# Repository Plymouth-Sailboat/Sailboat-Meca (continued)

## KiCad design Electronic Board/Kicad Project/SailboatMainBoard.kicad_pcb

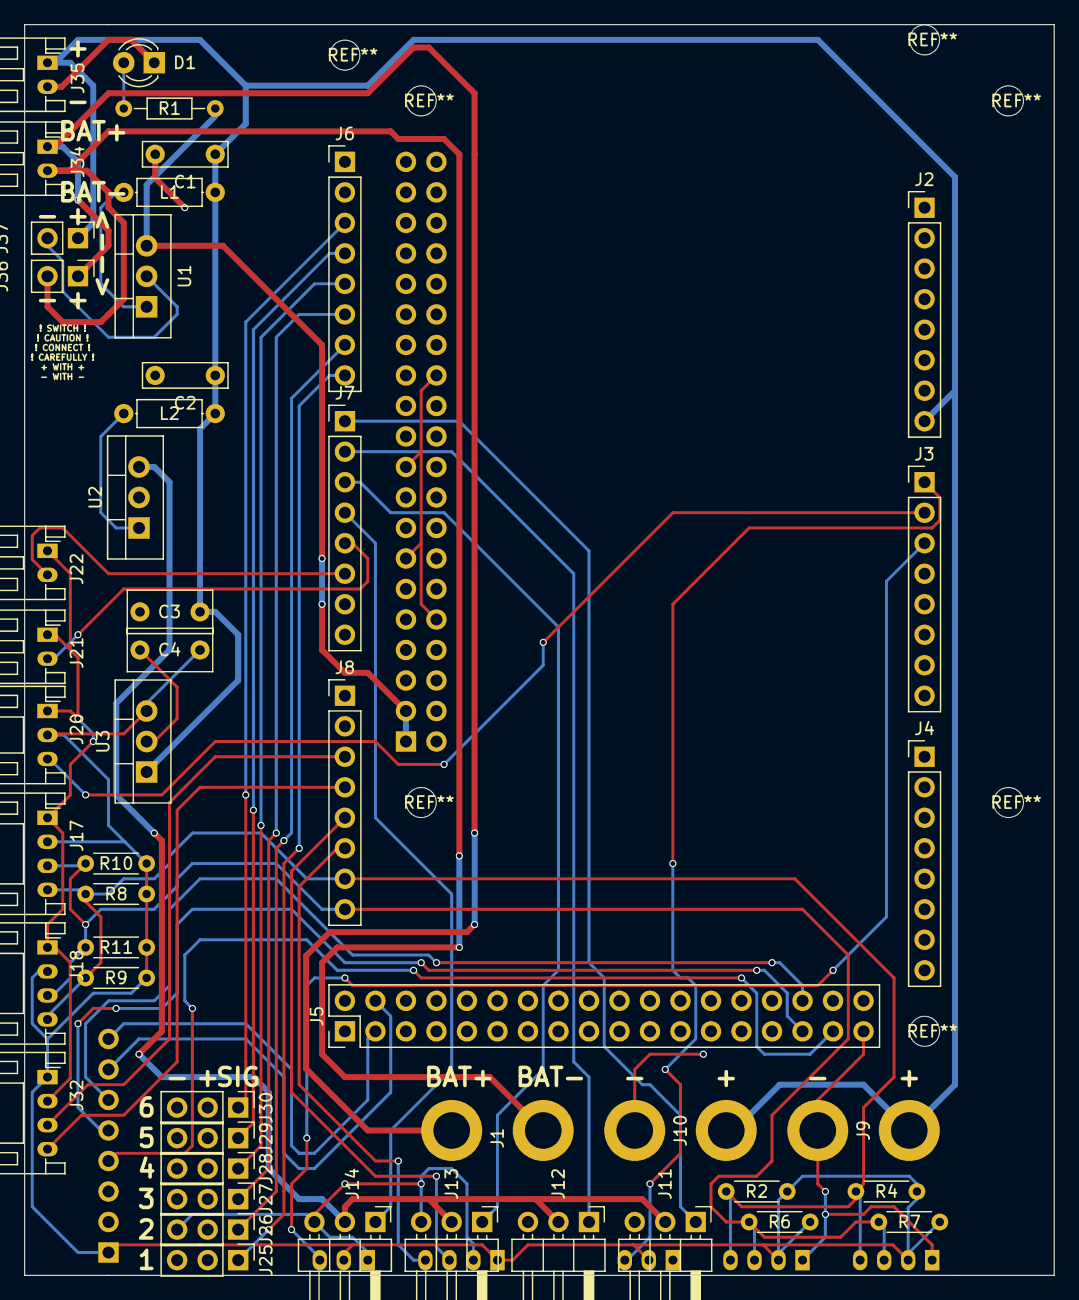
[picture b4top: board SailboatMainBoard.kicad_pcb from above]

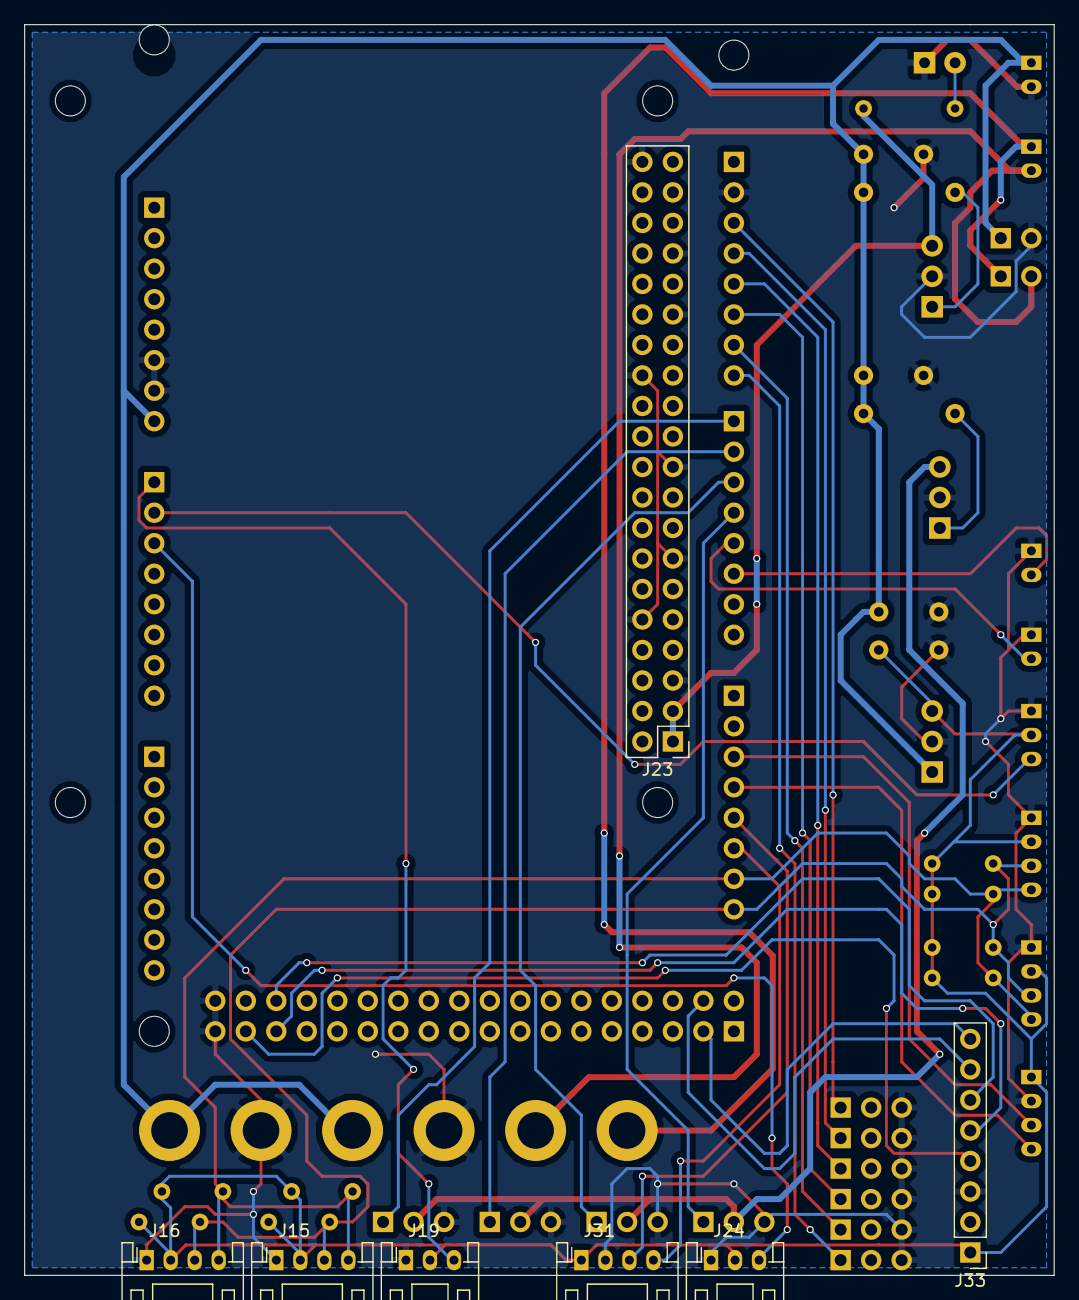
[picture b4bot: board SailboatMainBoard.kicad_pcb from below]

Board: 2 copper layers, 85.7 x 104.1 mm, 56 parts (7 on the bottom side), 36 nets.

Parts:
C1, C2: 4.7uF; C_Rect_L7.0mm_W2.0mm_P5.00mm
C3: 0.33uF; C_Rect_L7.0mm_W3.5mm_P5.00mm
C4: 0.1uF; C_Rect_L7.0mm_W3.5mm_P5.00mm
D1: G; LED_D3.0mm
J1, J9, J10: Conn_01x02; BAT-CONN
J2, J3, J4, J6, J7, J8: Conn_01x08; Pin_Header_Straight_1x08_Pitch2.54mm
J5: Conn_02x18_Odd_Even; Pin_Header_Straight_2x18_Pitch2.54mm
J11, J12, J13, J14: Conn_01x03_Male; Pin_Header_Angled_1x03_Pitch2.54mm
J15, J16, J17, J18, J31, J32: Conn_01x04; JST_PH_S4B-PH-K_04x2.00mm_Angled
J19, J20, J24: Conn_01x03; JST_PH_S3B-PH-K_03x2.00mm_Angled
J21, J22, J34, J35: Conn_01x02; JST_PH_S2B-PH-K_02x2.00mm_Angled
J23: Conn_02x20_Odd_Even; Pin_Header_Straight_2x20_Pitch2.54mm
J25, J26, J27, J28, J29, J30: Conn_01x03_Female; Socket_Strip_Straight_1x03_Pitch2.54mm
J33: Conn_01x08_Female; Socket_Strip_Straight_1x08_Pitch2.54mm
J36, J37: Conn_01x02; Pin_Header_Straight_1x02_Pitch2.54mm
L1, L2: 3.3uH; L_Axial_L5.3mm_D2.2mm_P7.62mm_Horizontal_Vishay_IM-1
R1: 330; R_Axial_DIN0204_L3.6mm_D1.6mm_P7.62mm_Horizontal
R2, R4, R6, R7, R8, R9, R10, R11: 4k7; R_Axial_DIN0204_L3.6mm_D1.6mm_P5.08mm_Horizontal
U1, U2, U3: L7805; TO-220-3_Vertical

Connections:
5V_RPi: J23.1, J23.3, R1.2, U1.3
/Connectors/5V-Sensors: C4.1, J15.2, J16.2, J17.2, J18.2, J19.2, J20.2, J24.2, J31.1, J32.1, J33.1, R2.1, R4.1, R6.1, R7.1, R8.1, R9.1, R10.1, R11.1, U3.3
/Connectors/5V-Servo: J11.2, J12.2, J13.2, J14.2, U2.3
A0: J3.1, J19.3
A1: J3.2, J20.3
A2: J3.3, J24.3
BAT+: C1.1, C2.1, C3.1, J2.8, J9.2, J10.2, J35.1, J37.1, L1.2, L2.2, U3.1
CD: J5.3, J33.8
CS: J5.4, J33.7
D0: J7.5, J21.2
D1: J7.6, J22.2
GND: C1.2, C2.2, C3.2, C4.2, D1.1, J2.6, J2.7, J5.35, J5.36, J6.2, J9.1, J10.1, J11.3, J12.3, J13.3, J14.3, J15.1, J16.1, J17.1, J18.1, J19.1, J20.1, J21.1, J22.1, J23.5, J23.10, J23.13, J23.19, J23.26, J23.29, J23.33, J23.40, J24.1, J25.3, J26.3, J27.3, J28.3, J29.3, J30.3, J31.2, J32.2, J33.3, J35.2, J37.2, U1.2, U2.2, U3.2
MISO: J5.31, J33.5
MOSI: J5.32, J33.6
unnamed: D1.2, R1.1
unnamed: J1.1, J34.1, J36.1
unnamed: J1.2, J34.2, J36.2
unnamed: L1.1, U1.1
unnamed: L2.1, U2.1
RC1: J6.8, J25.1
RC2: J6.7, J26.1
RC3: J6.6, J27.1
RC4: J6.5, J28.1
RC5: J6.4, J29.1
RC6: J6.3, J30.1
RX_1: J8.6, J31.4
RX_2: J8.4, J32.4
Rudder: J7.2, J12.1
SCK: J5.33, J33.4
SCL: J8.8, J15.3, J16.3, J17.3, J18.3, R6.2, R7.2, R10.2, R11.2
SDA: J8.7, J15.4, J16.4, J17.4, J18.4, R2.2, R4.2, R8.2, R9.2
Sail: J7.1, J11.1
Servo1: J7.3, J13.1
Servo2: J7.4, J14.1
TX_1: J8.5, J31.3
TX_2: J8.3, J32.3

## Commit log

2018-03-22 Separated Boards for smaller factor
2018-03-23 Finished board-v0.1
2018-03-26 Finished 2 boards and submitted for manufacturing
2018-03-28 BOM of the boat
2018-03-28 Updated wrong sources to BOM
2018-04-03 3D and png of final boards
2018-04-19 Added GPS Box 3Ds
2018-04-19 Hotfix on raspberry pi Card Radio interface
2018-04-19 Hotfix again for Radio on Rasbperry pi
2018-04-20 Hotfix GPS Box for waterproofing and screws. Xsens box added
2018-05-29 Cleaned up, and added security, text and better usability, preparation for board v2
2018-05-29 Prepared gerber and pdf files
2018-06-01 Minor changes and recompiled gerber, pdf and 3D
2018-06-01 Recompiled RPi
2018-06-01 Changed size to be smaller than 100mm
2018-06-04 Updated BOM for new board and wrong products
2018-06-05 spelling mistakes
2018-07-23 New board bug fix
2018-09-13 added decoupler capacitor for voltage measurements and added connectors to arduino
2018-09-13 Beginning a small control box with raspberry pi zero and naked mega 4
2018-09-13 Removed the arduino. Why keep it?? Doesn't make sense :/
2018-09-14 Components installed for a working rpi0 shield for sailboat
2018-09-14 Finished tracing the RPi0 Board and plotted the gerbers, ready for production
2018-12-03 Began RPI0 board
2019-06-11 Updated version of Kicad, rendered images and BOM
2019-06-11 Added BOM of the RPI
2019-06-11 Upgrade Kicad Version and PDF Schematics
